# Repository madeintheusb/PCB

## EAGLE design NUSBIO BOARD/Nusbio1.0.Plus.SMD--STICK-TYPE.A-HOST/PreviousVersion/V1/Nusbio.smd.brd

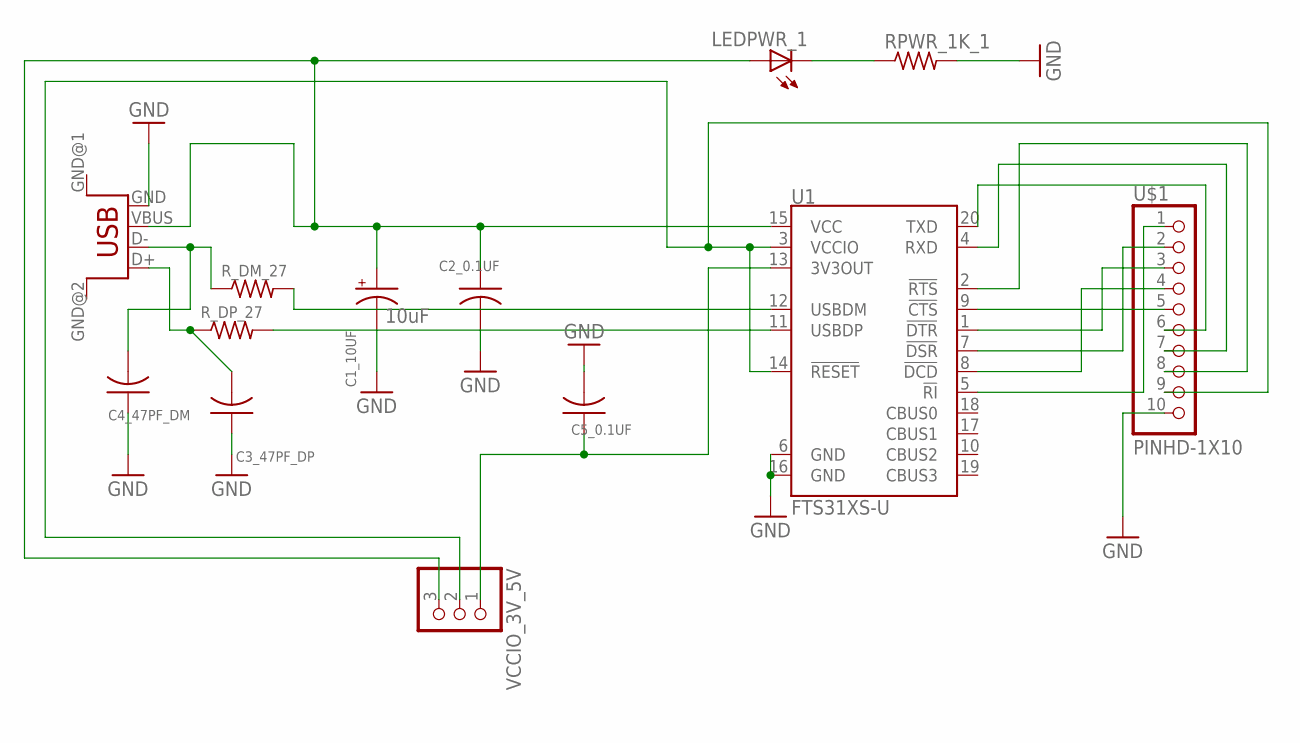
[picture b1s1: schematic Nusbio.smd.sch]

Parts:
C1_10UF: 10uF; EIA3216
C2_0.1UF, C3_47PF_DP, C4_47PF_DM, C5_0.1UF: C-USC1206; C1206
LEDPWR_1: LEDCHIPLED_0805; CHIPLED_0805
RPWR_1K_1: R-US_R0805; R0805
R_DM_27: R-US_R0805; R0805
R_DP_27: R-US_R0805; R0805
U1: FTS31XS-U; SSOP20_L
U$1: PINHD-1X10; 1X10-BIG
USB_FEMALE: USB; USB-FEMALE-A-PTH
VCCIO_3V_5V: PINHD-1X3; 1X03

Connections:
GND: C1_10UF.C (-), C2_0.1UF.2, C3_47PF_DP.1, C4_47PF_DM.1, C5_0.1UF.2, RPWR_1K_1.2, U1.6 (GND), U1.16 (GND), U$1.10, USB_FEMALE.GND
unnamed: C1_10UF.A (+), C2_0.1UF.1, LEDPWR_1.A, U1.15 (VCC), USB_FEMALE.VBUS, VCCIO_3V_5V.3
unnamed: C5_0.1UF.1, U1.13 (3V3OUT), VCCIO_3V_5V.1
unnamed: LEDPWR_1.C, RPWR_1K_1.1
unnamed: R_DM_27.2, U1.12 (USBDM)
unnamed: R_DP_27.2, U1.11 (USBDP)
unnamed: U1.20 (TXD), U$1.6
unnamed: U1.7 (!DSR), U$1.2
unnamed: U1.5 (!RI), U$1.1
unnamed: U1.1 (!DTR), U$1.3
unnamed: U1.8 (!DCD), U$1.4
unnamed: U1.9 (!CTS), U$1.5
unnamed: U1.4 (RXD), U$1.7
unnamed: U1.2 (!RTS), U$1.8
unnamed: U1.3 (VCCIO), U1.14 (!RESET), U$1.9, VCCIO_3V_5V.2
unnamed: C3_47PF_DP.2, R_DP_27.1, USB_FEMALE.D+
unnamed: C4_47PF_DM.2, R_DM_27.1, USB_FEMALE.D-

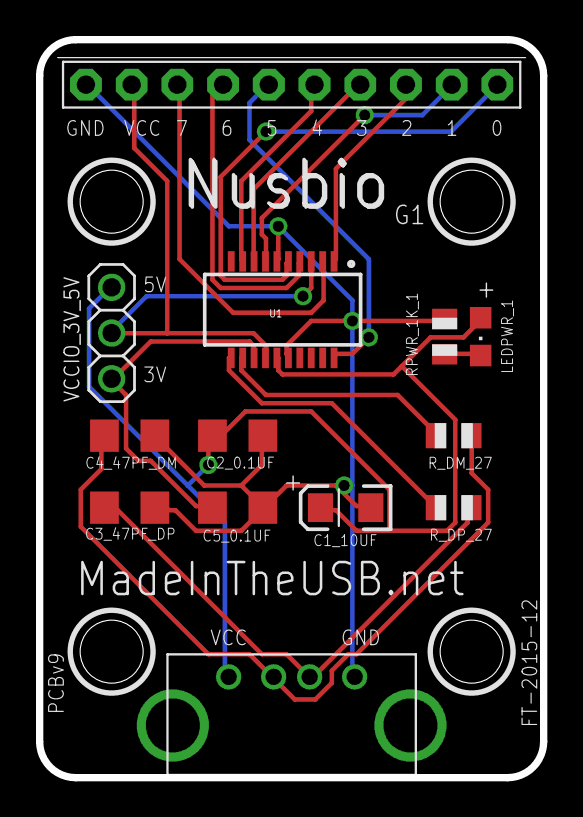
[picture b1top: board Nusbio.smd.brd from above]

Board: 2 copper layers, 28.0 x 41.0 mm, 13 parts (0 on the bottom side), 17 nets.

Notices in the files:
parts and their libraries:
SparkFun-Capacitors: Licensing: Creative Commons ShareAlike 4.0 International - https://creativecommons.org/licenses/by-sa/4.0
microbuilder: This work is placed in the public domain, and may be freely used for commercial and non-commercial work with the following conditions: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
